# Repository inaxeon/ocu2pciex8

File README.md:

# OCuLink to PCIe x4 Adapter

#### Description

This repository contains the design files for a PCIe x4 (x8 physical) to OCuLink adapter I designed to solve some difficult PC build problems some time ago.

It is strictly PCIe Gen 3 or less only.

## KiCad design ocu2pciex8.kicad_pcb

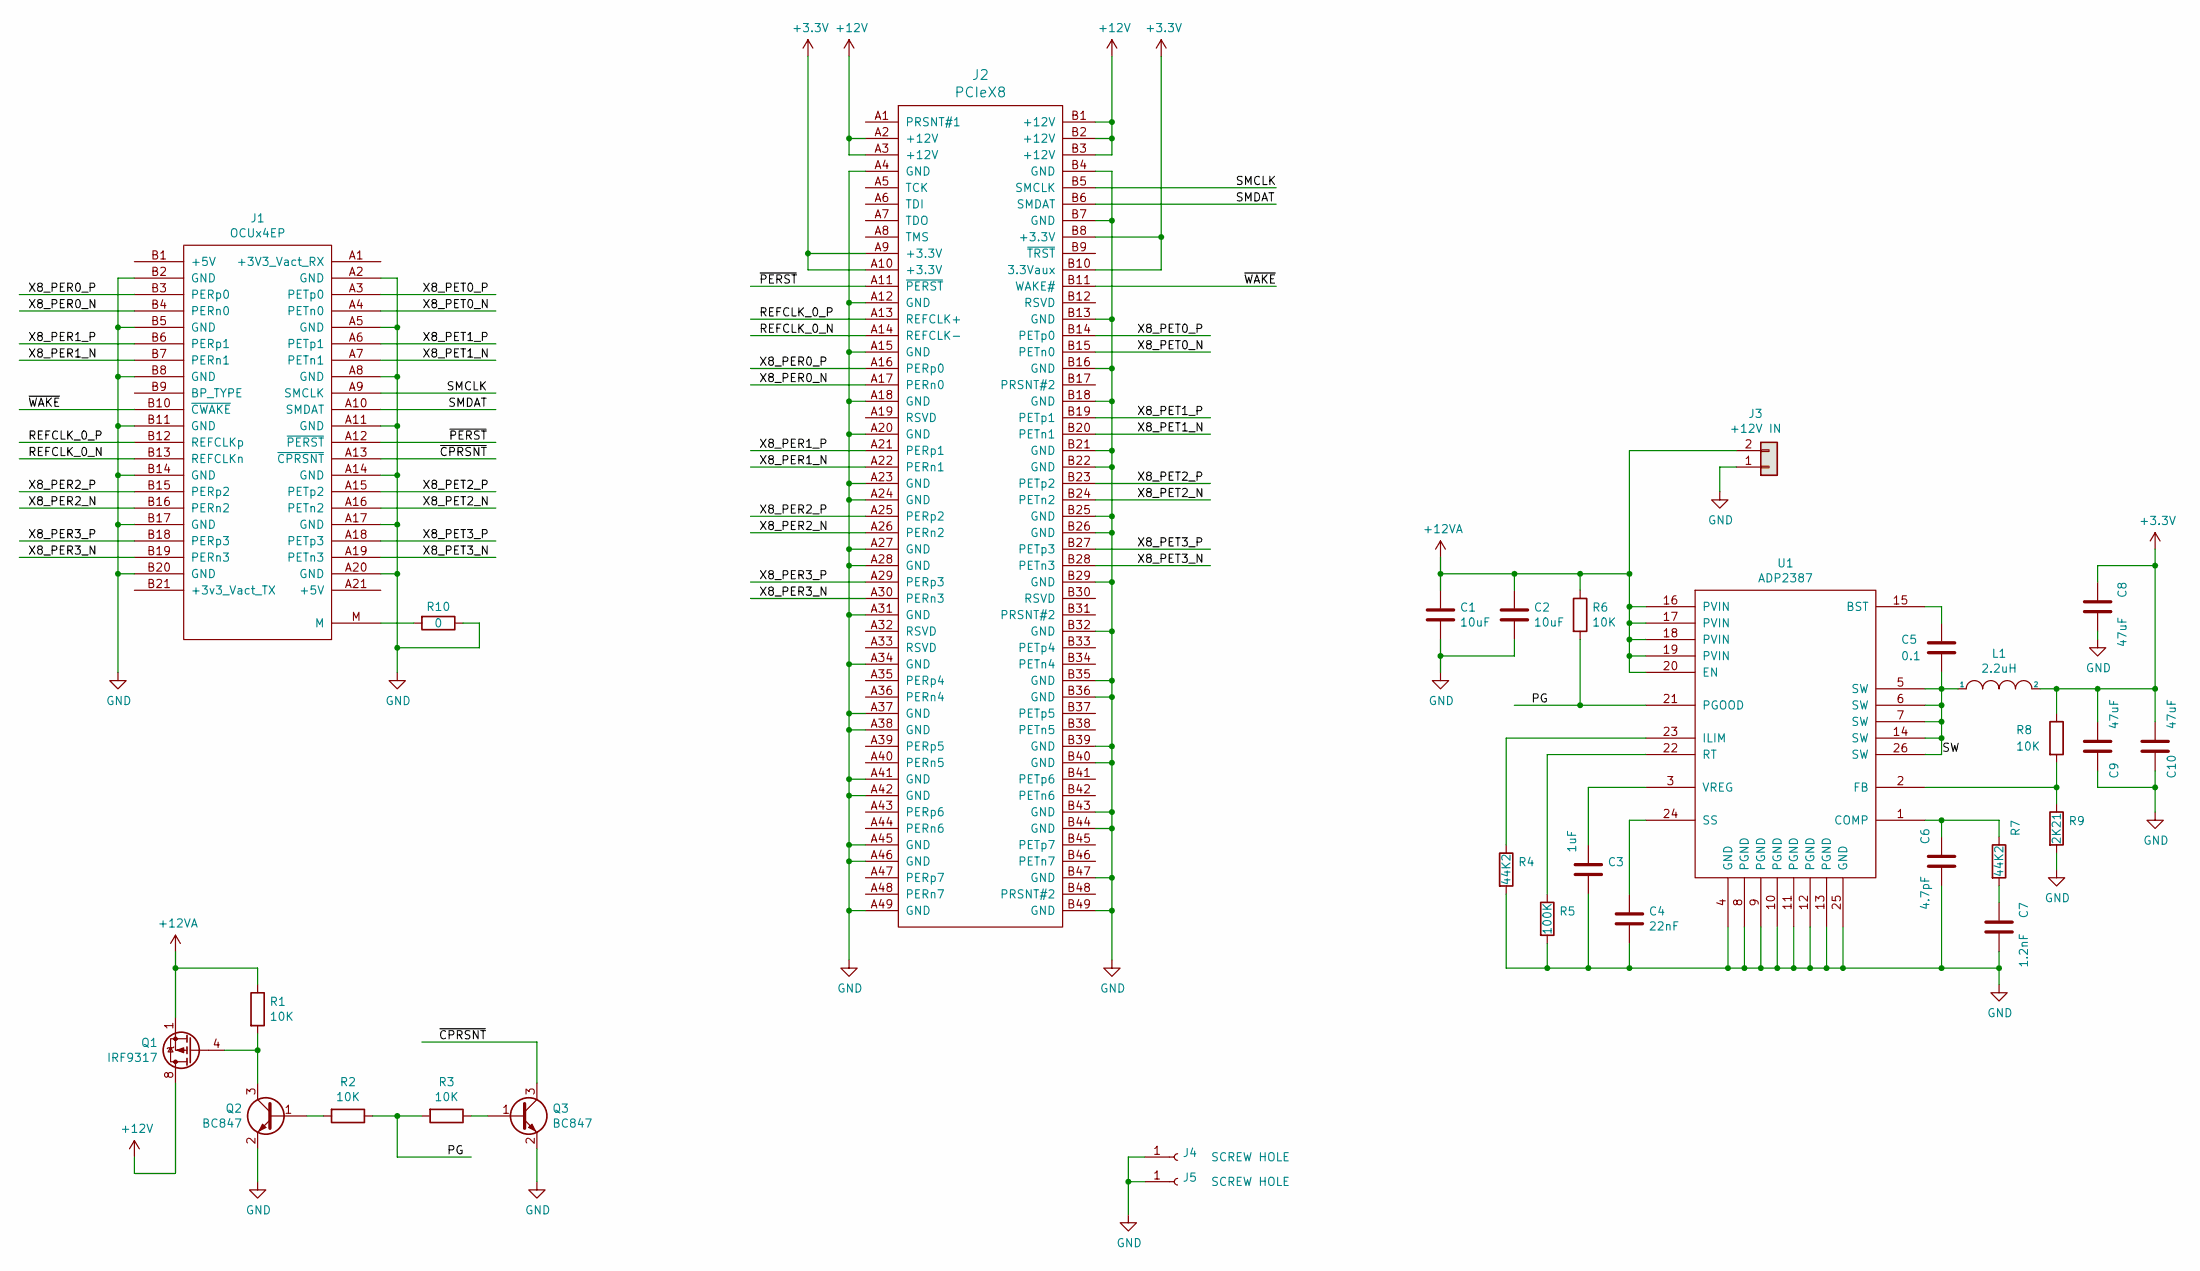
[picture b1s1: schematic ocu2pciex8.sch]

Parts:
C1, C2: 10uF; C_1210_3225Metric
C3: 1uF; C_0603_1608Metric
C4: 22nF; C_0603_1608Metric
C5: 0.1; C_0603_1608Metric
C6: 4.7pF; C_0603_1608Metric
C7: 1.2nF; C_0603_1608Metric
C8, C9, C10: 47uF; C_1210_3225Metric
J1: OCUx4EP; G14A421211112HR
J2: PCIeX8; PCIE-098-02-F-D-TH
J3: +12V IN; MINI_FIT_JR_1X2_RA
J4, J5: SCREW HOLE; SCREWHOLE
L1: 2.2uH; L_Vishay_IHLP-2525
Q1: IRF9317; SOIC-8_3.9x4.9mm_P1.27mm
Q2, Q3: BC847; SOT-23
R1, R2, R3, R6, R8: 10K; R_0603_1608Metric
R4, R7: 44K2; R_0603_1608Metric
R5: 100K; R_0603_1608Metric
R9: 2K21; R_0603_1608Metric
R10: 0; R_0603_1608Metric
U1: ADP2387; QFN-24-2EP_4x4mm_P0.5mm_EP2.6x2.6mm

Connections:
+3V3: C8.1, C9.1, C10.1, J2.A9 (+3.3V), J2.A10 (+3.3V), J2.B8 (+3.3V), J2.B10 (3.3Vaux), L1.2, R8.1
+12V: J2.A2 (+12V), J2.A3 (+12V), J2.B1 (+12V), J2.B2 (+12V), J2.B3 (+12V), Q1.5 (D), Q1.6 (D), Q1.7 (D), Q1.8 (D)
+12VA: C1.1, C2.1, J3.2, Q1.1 (S), Q1.2 (S), Q1.3 (S), R1.1, R6.1, U1.16 (PVIN), U1.17 (PVIN), U1.18 (PVIN), U1.19 (PVIN), U1.20 (EN)
/PG: R2.1, R3.2, R6.2, U1.21 (PGOOD)
/REFCLK_0_N: J1.B13 (REFCLKn), J2.A14 (REFCLK-)
/REFCLK_0_P: J1.B12 (REFCLKp), J2.A13 (REFCLK+)
/SMCLK: J1.A9 (SMCLK), J2.B5 (SMCLK)
/SMDAT: J1.A10 (SMDAT), J2.B6 (SMDAT)
/SW: C5.2, L1.1, U1.5 (SW), U1.6 (SW), U1.7 (SW), U1.14 (SW), U1.26 (SW)
/X8_PER0_N: J1.B4 (PERn0), J2.A17 (PERn0)
/X8_PER0_P: J1.B3 (PERp0), J2.A16 (PERp0)
/X8_PER1_N: J1.B7 (PERn1), J2.A22 (PERn1)
/X8_PER1_P: J1.B6 (PERp1), J2.A21 (PERp1)
/X8_PER2_N: J1.B16 (PERn2), J2.A26 (PERn2)
/X8_PER2_P: J1.B15 (PERp2), J2.A25 (PERp2)
/X8_PER3_N: J1.B19 (PERn3), J2.A30 (PERn3)
/X8_PER3_P: J1.B18 (PERp3), J2.A29 (PERp3)
/X8_PET0_N: J1.A4 (PETn0), J2.B15 (PETn0)
/X8_PET0_P: J1.A3 (PETp0), J2.B14 (PETp0)
/X8_PET1_N: J1.A7 (PETn1), J2.B20 (PETn1)
/X8_PET1_P: J1.A6 (PETp1), J2.B19 (PETp1)
/X8_PET2_N: J1.A16 (PETn2), J2.B24 (PETn2)
/X8_PET2_P: J1.A15 (PETp2), J2.B23 (PETp2)
/X8_PET3_N: J1.A19 (PETn3), J2.B28 (PETn3)
/X8_PET3_P: J1.A18 (PETp3), J2.B27 (PETp3)
/~CPRSNT: J1.A13 (~CPRSNT), Q3.3 (C)
/~PERST: J1.A12 (~PERST), J2.A11 (~PERST)
/~WAKE: J1.B10 (~CWAKE), J2.B11 (WAKE#)
GND: C1.2, C2.2, C3.1, C4.2, C6.2, C7.2, C8.2, C9.2, C10.2, J1.A2 (GND), J1.A5 (GND), J1.A8 (GND), J1.A11 (GND), J1.A14 (GND), J1.A17 (GND), J1.A20 (GND), J1.B2 (GND), J1.B5 (GND), J1.B8 (GND), J1.B11 (GND), J1.B14 (GND), J1.B17 (GND), J1.B20 (GND), J2.A4 (GND), J2.A12 (GND), J2.A15 (GND), J2.A18 (GND), J2.A20 (GND), J2.A23 (GND), J2.A24 (GND), J2.A27 (GND), J2.A28 (GND), J2.A31 (GND), J2.A34 (GND), J2.A37 (GND), J2.A38 (GND), J2.A41 (GND), J2.A42 (GND), J2.A45 (GND), J2.A46 (GND), J2.A49 (GND), J2.B4 (GND), J2.B7 (GND), J2.B13 (GND), J2.B16 (GND), J2.B18 (GND), J2.B21 (GND), J2.B22 (GND), J2.B25 (GND), J2.B26 (GND), J2.B29 (GND), J2.B32 (GND), J2.B35 (GND), J2.B36 (GND), J2.B39 (GND), J2.B40 (GND), J2.B43 (GND), J2.B44 (GND), J2.B47 (GND), J2.B49 (GND), J3.1, J4.1, J5.1, Q2.2 (E), Q3.2 (E), R4.2, R5.2, R9.2, R10.1, U1.4 (GND), U1.8 (PGND), U1.9 (PGND), U1.10 (PGND), U1.11 (PGND), U1.12 (PGND), U1.13 (PGND), U1.25 (GND)
unnamed: C3.2, U1.3 (VREG)
unnamed: C4.1, U1.24 (SS)
unnamed: C5.1, U1.15 (BST)
unnamed: C6.1, R7.1, U1.1 (COMP)
unnamed: C7.1, R7.2
unnamed: J1.M, R10.2
unnamed: Q1.4 (G), Q2.3 (C), R1.2
unnamed: Q2.1 (B), R2.2
unnamed: Q3.1 (B), R3.1
unnamed: R4.1, U1.23 (ILIM)
unnamed: R5.1, U1.22 (RT)
unnamed: R8.2, R9.1, U1.2 (FB)

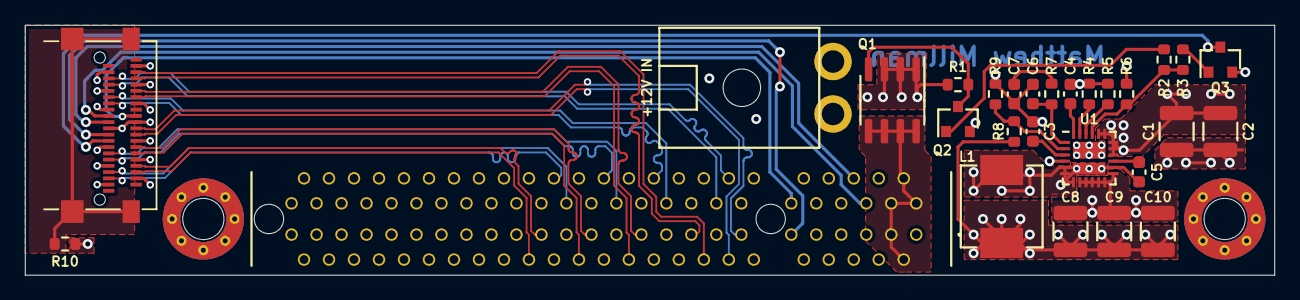
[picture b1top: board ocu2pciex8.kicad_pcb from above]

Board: 4 copper layers, 100.0 x 20.0 mm, 30 parts (0 on the bottom side), 41 nets.

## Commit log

2023-03-09 Added schematic
